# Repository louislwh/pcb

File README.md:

this is my pcb design design
# pcb

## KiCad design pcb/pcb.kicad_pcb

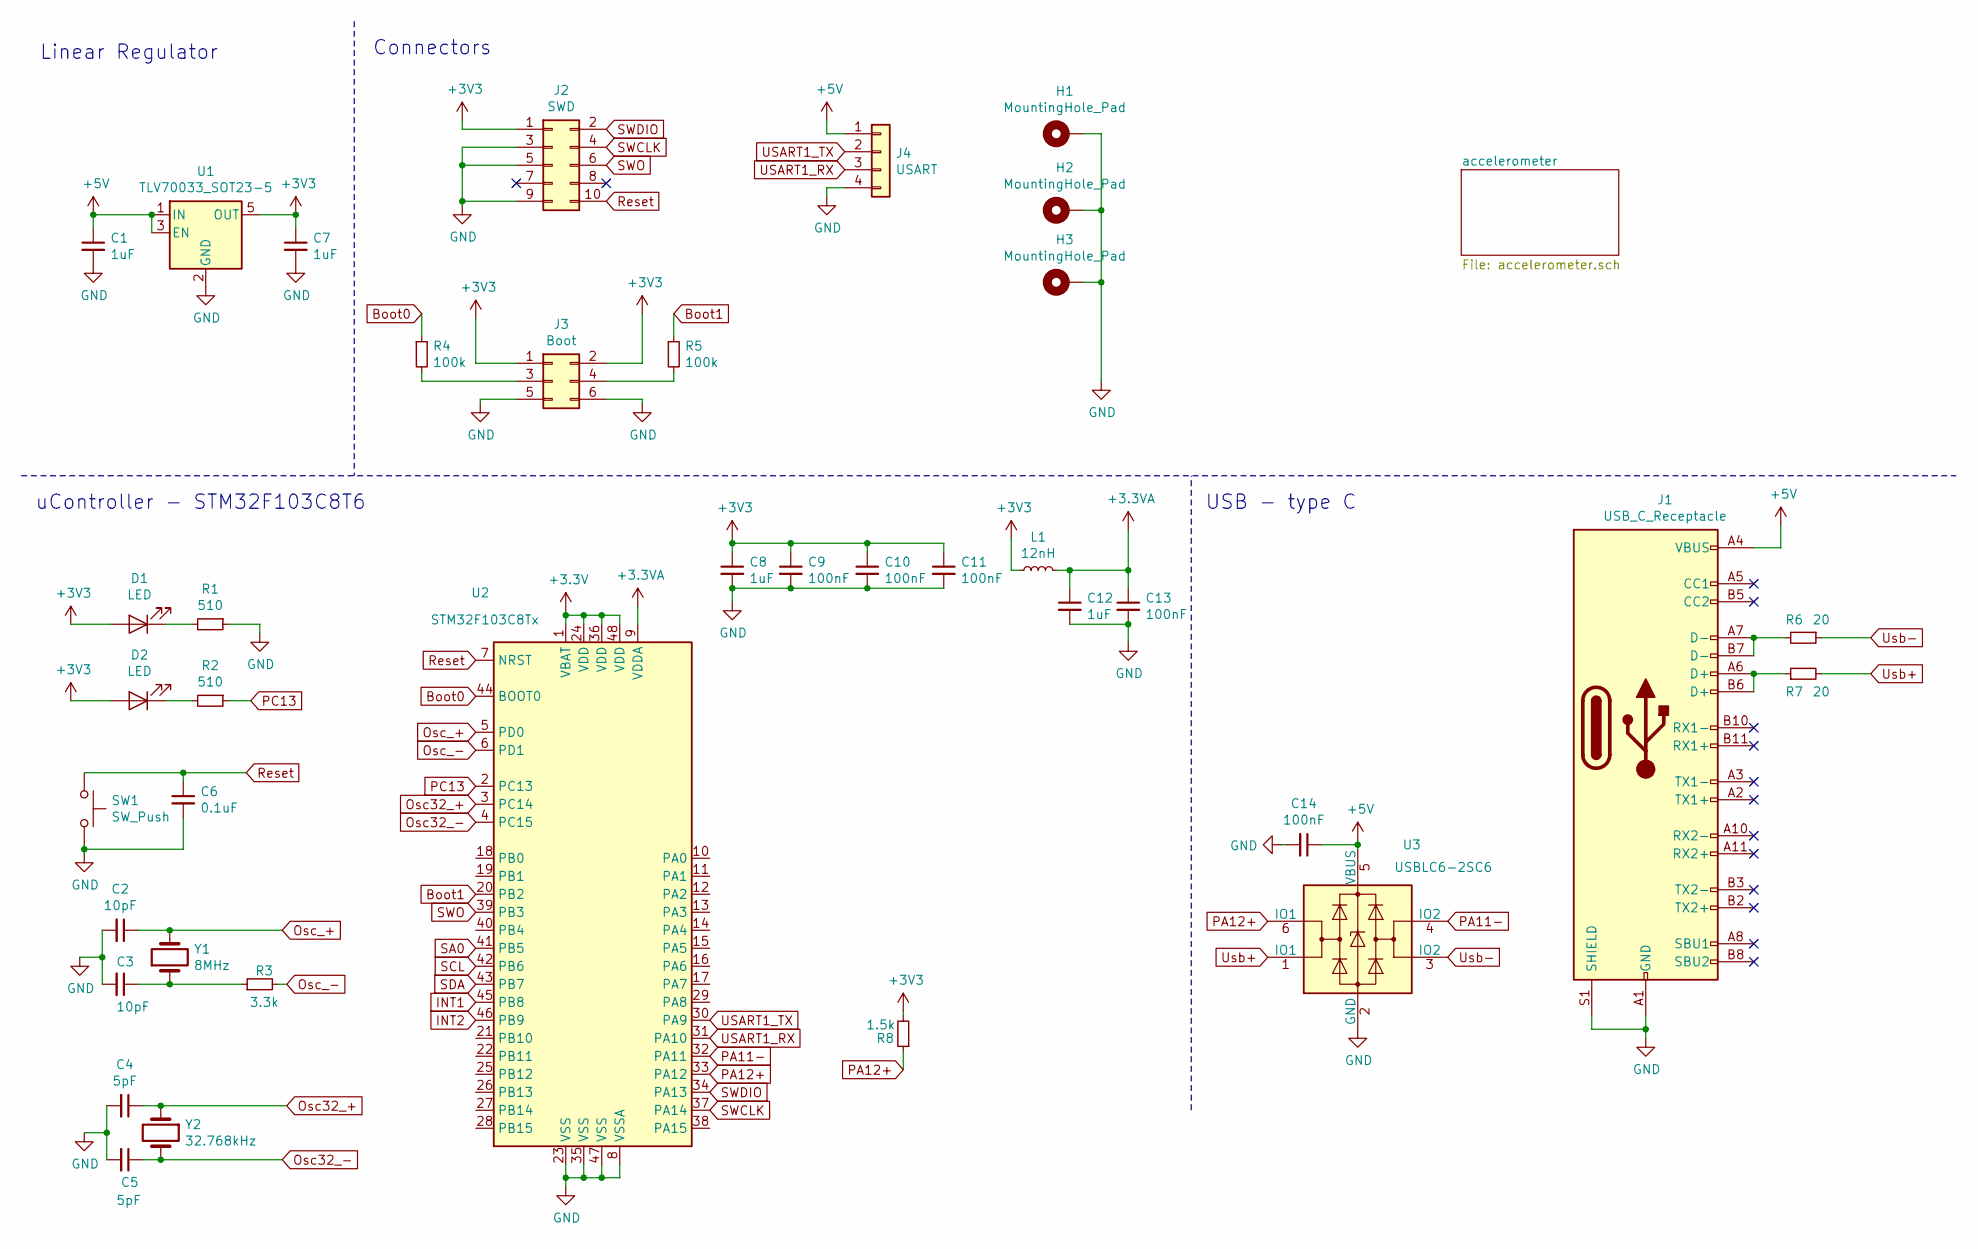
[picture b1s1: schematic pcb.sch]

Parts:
C1, C7, C8, C12: 1uF; C_0402_1005Metric; LCSC part # C52923
C2, C3: 10pF; C_0402_1005Metric; LCSC part # C32949
C4, C5: 5pF; C_0402_1005Metric; LCSC part # C318616
C6: 0.1uF; C_0402_1005Metric; LCSC part # C1525
C9, C10, C11, C13, C14: 100nF; C_0402_1005Metric; LCSC part # C1525
D1, D2: LED; LED_0603_1608Metric; LCSC part # C72038
H1, H2, H3: MountingHole_Pad; MountingHole_3.2mm_M3_Pad_Via
J1: USB_C_Receptacle; USB_C_Receptacle_GCT_USB4085
J2: SWD; PinHeader_2x05_P2.54mm_Vertical_SMD
J3: Boot; PinHeader_2x03_P2.54mm_Vertical
J4: USART; PinHeader_1x04_P2.54mm_Vertical
L1: 12nH; L_0402_1005Metric; LCSC part # C24563
R1, R2: 510; R_0402_1005Metric; LCSC part # C25123
R3: 3.3k; R_0402_1005Metric; LCSC part # C25890
R4, R5: 100k; R_0402_1005Metric; LCSC part # C25741
R6, R7: 20; R_0402_1005Metric; LCSC part # C25089
R8: 1.5k; R_0402_1005Metric; LCSC part # C25867
SW1: SW_Push; SW_SPST_B3SL-1002P; LCSC part # C318887
U1: TLV70033_SOT23-5; SOT-23-5; LCSC part # C132090
U2: STM32F103C8Tx; LQFP-48_7x7mm_P0.5mm; LCSC part # C8734
U3: USBLC6-2SC6; SOT-23-6; LCSC part # C7519
Y1: 8MHz; Crystal_SMD_5032-2Pin_5.0x3.2mm; LCSC part # C115962
Y2: 32.768kHz; Crystal_SMD_3215-2Pin_3.2x1.5mm; LCSC part # C48615

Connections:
+3.3VA: C12.1, C13.1, L1.2, U2.9 (VDDA)
+5V: C1.1, C14.1, J1.A4 (VBUS), J1.A9 (VBUS), J1.B4 (VBUS), J1.B9 (VBUS), J4.1, U1.1 (IN), U1.3 (EN), U3.5 (VBUS)
Boot0: R4.1, U2.44 (BOOT0)
Boot1: R5.1, U2.20 (PB2)
GND: C1.2, C2.2, C3.2, C4.2, C5.2, C6.2, C7.2, C8.2, C9.2, C10.2, C11.2, C12.2, C13.2, C14.2, H1.1, H2.1, H3.1, J1.A1 (GND), J1.A12 (GND), J1.B1 (GND), J1.B12 (GND), J1.S1 (SHIELD), J2.3, J2.5, J2.9, J3.5, J3.6, J4.4, R1.1, SW1.2, U1.2 (GND), U2.8 (VSSA), U2.23 (VSS), U2.35 (VSS), U2.47 (VSS), U3.2 (GND); also elsewhere on the board
INT1: U2.45 (PB8); also elsewhere on the board
INT2: U2.46 (PB9); also elsewhere on the board
unnamed: C3.1, R3.1, Y1.1
unnamed: D1.1 (K), R1.2
unnamed: D2.1 (K), R2.2
unnamed: J1.A6 (D+), J1.B6 (D+), R7.1
unnamed: J1.A7 (D-), J1.B7 (D-), R6.2
unnamed: J3.3, R4.2
unnamed: J3.4, R5.2
Osc32_+: C4.1, U2.3 (PC14), Y2.1
Osc32_-: C5.1, U2.4 (PC15), Y2.2
Osc_+: C2.1, U2.5 (PD0), Y1.2
Osc_-: R3.2, U2.6 (PD1)
PA11-: U2.32 (PA11), U3.4 (IO2)
PA12+: R8.1, U2.33 (PA12), U3.6 (IO1)
PC13: R2.1, U2.2 (PC13)
Reset: C6.1, J2.10, SW1.1, U2.7 (NRST)
SA0: U2.41 (PB5); also elsewhere on the board
SCL: U2.42 (PB6); also elsewhere on the board
SDA: U2.43 (PB7); also elsewhere on the board
SWCLK: J2.4, U2.37 (PA14)
SWDIO: J2.2, U2.34 (PA13)
SWO: J2.6, U2.39 (PB3)
USART1_RX: J4.3, U2.31 (PA10)
USART1_TX: J4.2, U2.30 (PA9)
Usb+: R7.2, U3.1 (IO1)
Usb-: R6.1, U3.3 (IO2)

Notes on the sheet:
USB - type C
uController - STM32F103C8T6
Linear Regulator
Connectors

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
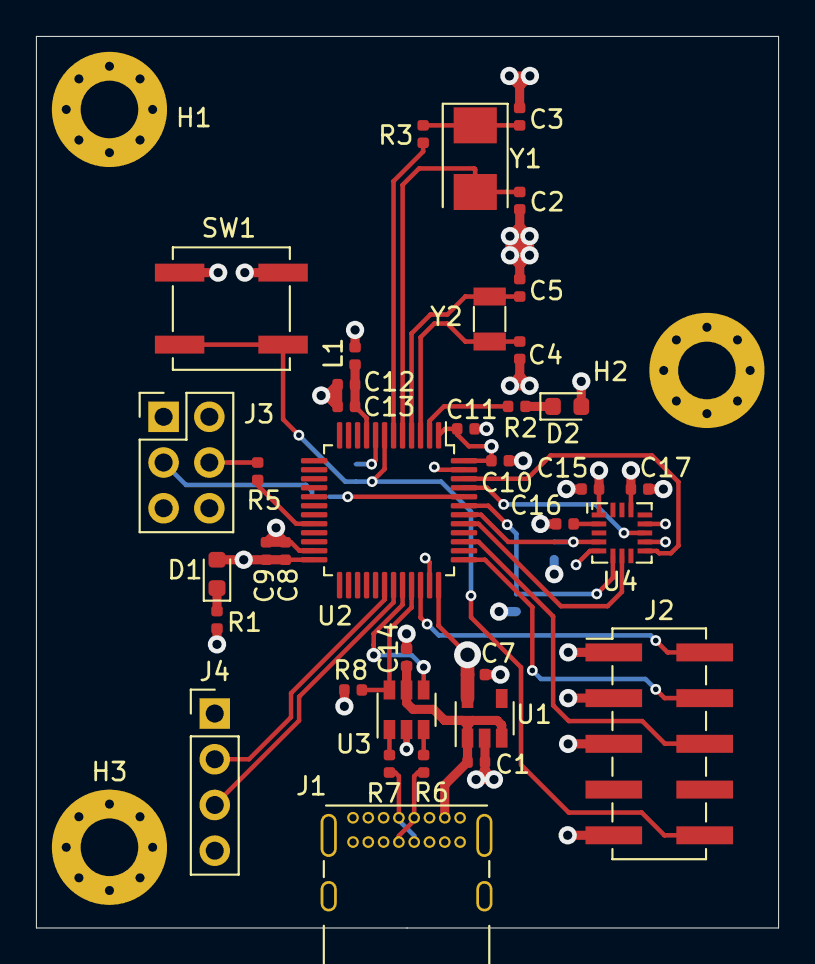
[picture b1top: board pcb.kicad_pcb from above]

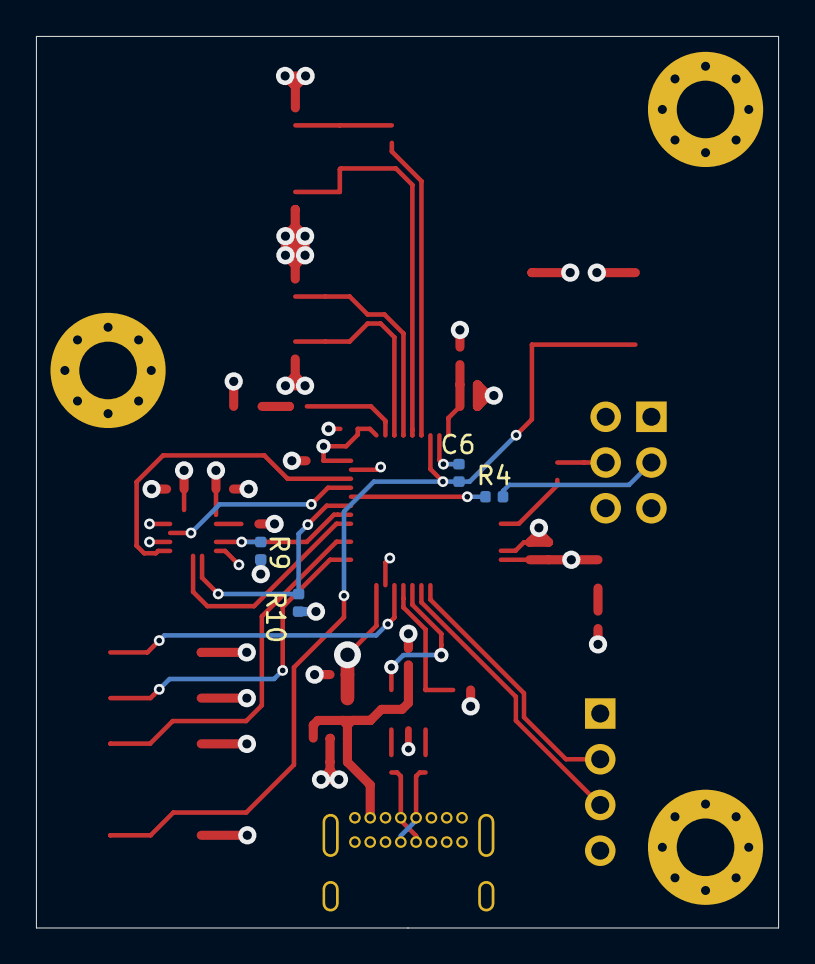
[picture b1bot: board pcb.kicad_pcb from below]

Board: 4 copper layers, 41.2 x 49.5 mm, 44 parts (4 on the bottom side), 34 nets.

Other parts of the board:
C15, C16: 0.1uF; C_0402_1005Metric
C17: 4.7uF; C_0402_1005Metric
R9, R10: 4.7k; R_0402_1005Metric
U4: MMA8451Q

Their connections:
BYP: C16.1, U4.2
GND: C15.2, C16.2, C17.1, U4.5, U4.10, U4.12; also elsewhere on the board
INT1: U4.11; also elsewhere on the board
INT2: U4.9; also elsewhere on the board
SA0: U4.7; also elsewhere on the board
SCL: R9.2, U4.4; also elsewhere on the board
SDA: R10.2, U4.6; also elsewhere on the board

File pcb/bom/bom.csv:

Reference, Quantity, Value, Footprint, Datasheet, LCSC part #
C17 ,1,"4.7uF","Capacitor_SMD:C_0402_1005Metric","~","C23733"
C2 C3 ,2,"10pF","Capacitor_SMD:C_0402_1005Metric","~","C32949"
C4 C5 ,2,"5pF","Capacitor_SMD:C_0402_1005Metric","~","C318616"
C6 C15 C16 ,3,"0.1uF","Capacitor_SMD:C_0402_1005Metric","~","C1525"
C8 C12 C1 C7 ,4,"1uF","Capacitor_SMD:C_0402_1005Metric","~","C52923"
C9 C10 C11 C13 C14 ,5,"100nF","Capacitor_SMD:C_0402_1005Metric","~","C1525"
D1 D2 ,2,"LED","LED_SMD:LED_0603_1608Metric","~","C72038"
H1 H2 H3 ,3,"MountingHole_Pad","MountingHole:MountingHole_3.2mm_M3_Pad_Via","~"
J1 ,1,"USB_C_Receptacle","Connector_USB:USB_C_Receptacle_GCT_USB4085","https://www.usb.org/sites/default/files/documents/usb_type-c.zip"
J2 ,1,"SWD","Connector_PinHeader_2.54mm:PinHeader_2x05_P2.54mm_Vertical_SMD","~"
J3 ,1,"Boot","Connector_PinHeader_2.54mm:PinHeader_2x03_P2.54mm_Vertical","~"
J4 ,1,"USART","Connector_PinHeader_2.54mm:PinHeader_1x04_P2.54mm_Vertical","~"
L1 ,1,"12nH","Inductor_SMD:L_0402_1005Metric","~","C24563"
R1 R2 ,2,"510","Resistor_SMD:R_0402_1005Metric","~","C25123"
R3 ,1,"3.3k","Resistor_SMD:R_0402_1005Metric","~","C25890"
R4 R5 ,2,"100k","Resistor_SMD:R_0402_1005Metric","~","C25741"
R6 R7 ,2,"20","Resistor_SMD:R_0402_1005Metric","~","C25089"
R8 ,1,"1.5k","Resistor_SMD:R_0402_1005Metric","~","C25867"
R9 R10 ,2,"4.7k","Resistor_SMD:R_0402_1005Metric","~","C25900"
SW1 ,1,"SW_Push","Button_Switch_SMD:SW_SPST_B3SL-1002P","~","C318887"
U1 ,1,"TLV70033_SOT23-5","Package_TO_SOT_SMD:SOT-23-5","http://www.ti.com/lit/ds/symlink/tlv700.pdf","C132090"
U2 ,1,"STM32F103C8Tx","Package_QFP:LQFP-48_7x7mm_P0.5mm","http://www.st.com/st-web-ui/static/active/en/resource/techni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","C8734"
U3 ,1,"USBLC6-2SC6","Package_TO_SOT_SMD:SOT-23-6","http://www2.st.com/resource/en/datasheet/CD00050750.pdf","C7519"
U4 ,1,"MMA8451Q","my_footprint:MMA8451Q","https://www.nxp.com/docs/en/data-sheet/MMA8451Q.pdf","C118083"
Y1 ,1,"8MHz","Crystal:Crystal_SMD_5032-2Pin_5.0x3.2mm","~","C115962"
Y2 ,1,"32.768kHz","Crystal:Crystal_SMD_3215-2Pin_3.2x1.5mm","~","C48615"
